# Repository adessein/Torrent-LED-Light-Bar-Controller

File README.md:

# Purpose
The purpose of this project is to create a Wifi controller for an orange Axixtech Torrent Led Light Bar.
This device is a safety light device that can be mounted on a vehicule for signaling danger, roadworks...
It is originaly delivered with a very simple control panel made of push buttons.

The purpose of this project is to create a system for the user to be able to control the light bar wirelessly, using his smartphone.

# Realisation

According to [the manual](../master/doc/TORRENT%20Lightbar%20Operation%20Manual.pdf) the bar is controlled by 15 wires. The voltage at these wires should either be 0 or 12V, respectively low and high level. Some wires should be hold at high level continuously of activating functions, more advanced ones requires mode selection by tapping several times on the wire (sending 12V pulses).

I have decided to make the electonic design as simple as possible: 
 - an ESP8266 is the main controllers: it creates a Wifi access point and sends a webpage to the client.
 - when the user select a function, the controller prepare the wire configuration state and pushes these states to shift registers.
 - since the voltae should be 12V, two Darlington NPN transistor arrays are used. Because they are NPN, they will be used to pull down the voltage when their emitter-base votage is positive. Which means that the controller should control using inversed logic (the shift registed should output 0V for the corresponding wire to be set to 12V and 3.3V for the wire to be set to 0V)

.

The ESP8266 micro-controller creates a Wifi access point.  
When connected to it, the user is redirected to a web page where he can change the illumination mode.  

## Code

The ESP8266 code contains the HTML page, therefore all the code is in one file [TorrentBar.ino](../master/TorrentBar/TorrentBar.ino).  
The webpage is also available in the file [TorrentBar.html](../master/doc/TorrentBar.html) for testing purposes.  

## Electronics

The circuit is rather simple, based on Darlington NPN transistor arrays and shift registers.  
The car battery supplies the 12V, which is reduced to 5V using a LM7805 voltage regulator.  
The 3.3V is either supplied by a LD1117V33 regulator (optional) or by the regulator located on the ESP8266 D1 Mini board.  

[My EDA project can be found here](https://easyeda.com/arnaud.dessein/torrent-light-bar)

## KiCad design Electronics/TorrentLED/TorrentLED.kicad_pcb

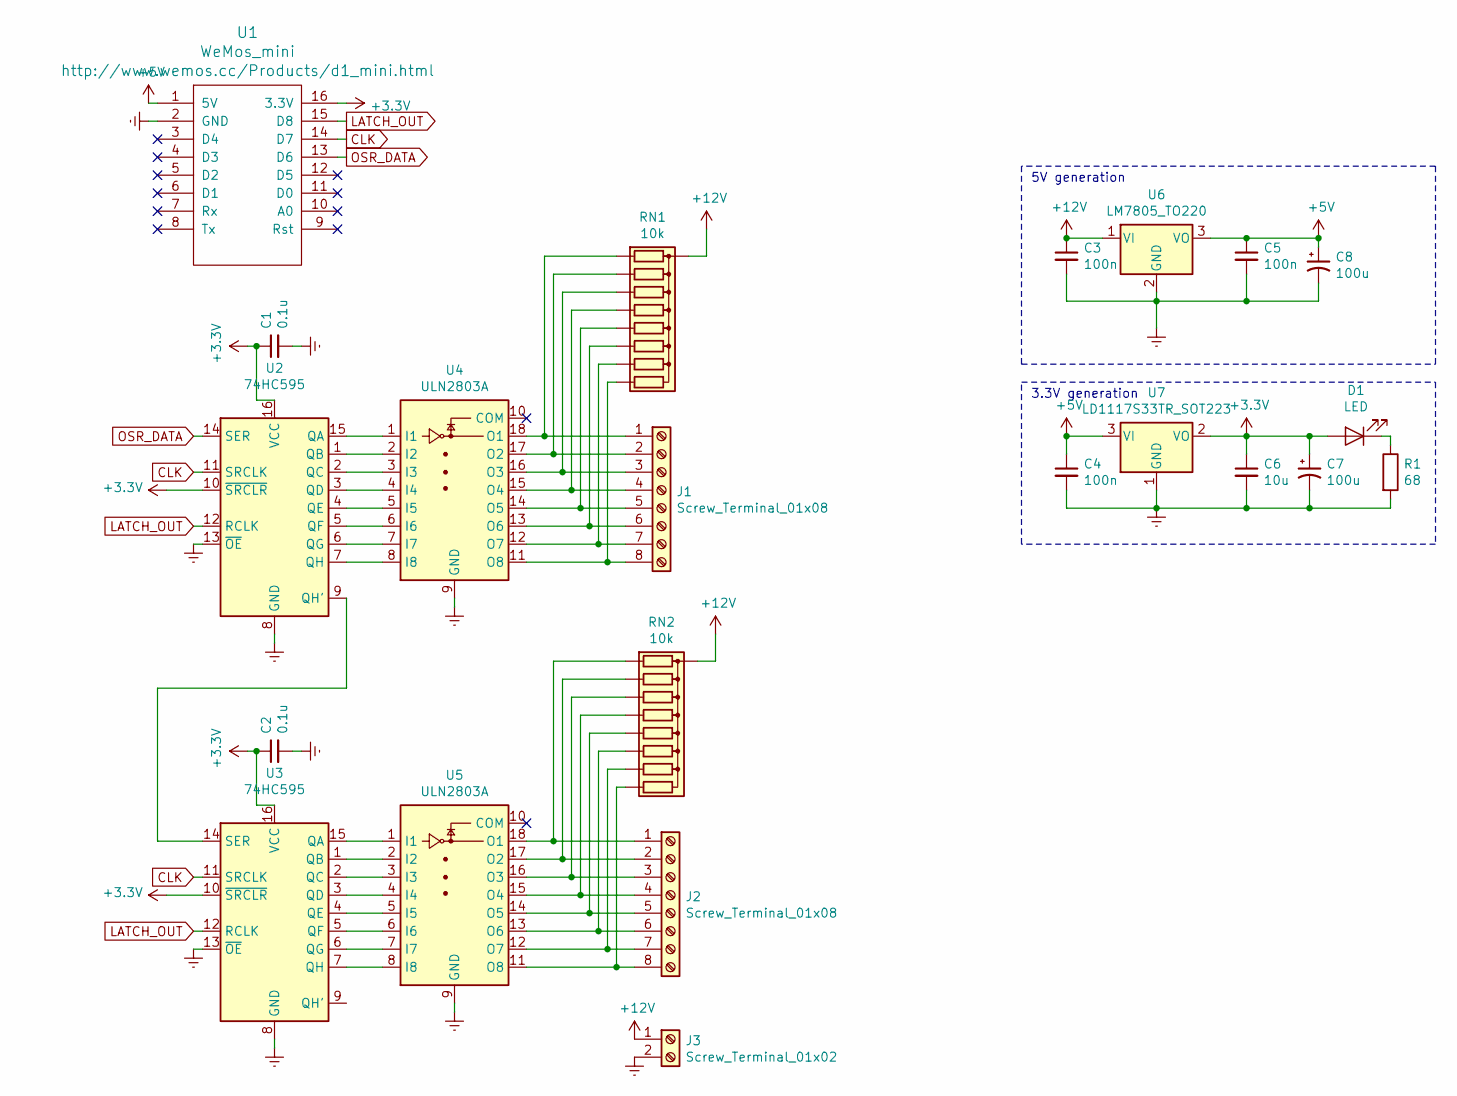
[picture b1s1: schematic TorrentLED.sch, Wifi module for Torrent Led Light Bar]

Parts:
C1, C2: 0.1u; C_Disc_D5.0mm_W2.5mm_P2.50mm
C3, C4, C5: 100n; C_Disc_D5.0mm_W2.5mm_P2.50mm
C6: 10u; C_Radial_D5.0mm_H11.0mm_P2.00mm
C7, C8: 100u; C_Radial_D6.3mm_H11.0mm_P2.50mm
D1: LED; LED_D3.0mm
J1, J2: Screw_Terminal_01x08; TerminalBlock_Phoenix_PT-1,5-8-5.0-H_1x08_P5.00mm_Horizontal
J3: Screw_Terminal_01x02; TerminalBlock_Phoenix_PT-1,5-2-5.0-H_1x02_P5.00mm_Horizontal
R1: 68; R_Axial_DIN0204_L3.6mm_D1.6mm_P7.62mm_Horizontal
RN1, RN2: 10k; R_Array_SIP9
U1: WeMos_mini; D1_mini_board
U2, U3: 74HC595; DIP-16_W7.62mm_Socket
U4, U5: ULN2803A; DIP-18_W7.62mm_Socket
U6: LM7805_TO220; TO-220-3_Vertical
U7: LD1117S33TR_SOT223; TO-220-3_Vertical

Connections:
+3V3: C1.1, C2.1, C6.1, C7.1, D1.2 (A), U1.16 (3.3V), U2.10 (~SRCLR), U2.16 (VCC), U3.10 (~SRCLR), U3.16 (VCC), U7.2 (VO)
+5V: C4.1, C5.1, C8.1, U1.1 (5V), U6.3 (VO), U7.3 (VI)
+12V: C3.1, J3.1, RN1.1 (common), RN2.1 (common), U6.1 (VI)
CLK: U1.14 (D7), U2.11 (SRCLK), U3.11 (SRCLK)
Earth: C1.2, C2.2, C3.2, C4.2, C5.2, C6.2, C7.2, C8.2, J3.2, R1.2, U1.2 (GND), U2.8 (GND), U2.13 (~OE), U3.8 (GND), U3.13 (~OE), U4.9 (GND), U5.9 (GND), U6.2 (GND), U7.1 (GND)
LATCH_OUT: U1.15 (D8), U2.12 (RCLK), U3.12 (RCLK)
unnamed: D1.1 (K), R1.1
unnamed: J1.1, RN1.2 (R1), U4.18 (O1)
unnamed: J1.2, RN1.3 (R2), U4.17 (O2)
unnamed: J1.3, RN1.4 (R3), U4.16 (O3)
unnamed: J1.4, RN1.5 (R4), U4.15 (O4)
unnamed: J1.5, RN1.6 (R5), U4.14 (O5)
unnamed: J1.6, RN1.7 (R6), U4.13 (O6)
unnamed: J1.7, RN1.8 (R7), U4.12 (O7)
unnamed: J1.8, RN1.9 (R8), U4.11 (O8)
unnamed: J2.1, RN2.2 (R1), U5.18 (O1)
unnamed: J2.2, RN2.3 (R2), U5.17 (O2)
unnamed: J2.3, RN2.4 (R3), U5.16 (O3)
unnamed: J2.4, RN2.5 (R4), U5.15 (O4)
unnamed: J2.5, RN2.6 (R5), U5.14 (O5)
unnamed: J2.6, RN2.7 (R6), U5.13 (O6)
unnamed: J2.7, RN2.8 (R7), U5.12 (O7)
unnamed: J2.8, RN2.9 (R8), U5.11 (O8)
unnamed: U2.1 (QB), U4.2 (I2)
unnamed: U2.2 (QC), U4.3 (I3)
unnamed: U2.3 (QD), U4.4 (I4)
unnamed: U2.4 (QE), U4.5 (I5)
unnamed: U2.5 (QF), U4.6 (I6)
unnamed: U2.6 (QG), U4.7 (I7)
unnamed: U2.7 (QH), U4.8 (I8)
unnamed: U2.9 (QH'), U3.14 (SER)
unnamed: U2.15 (QA), U4.1 (I1)
unnamed: U3.1 (QB), U5.2 (I2)
unnamed: U3.2 (QC), U5.3 (I3)
unnamed: U3.3 (QD), U5.4 (I4)
unnamed: U3.4 (QE), U5.5 (I5)
unnamed: U3.5 (QF), U5.6 (I6)
unnamed: U3.6 (QG), U5.7 (I7)
unnamed: U3.7 (QH), U5.8 (I8)
unnamed: U3.15 (QA), U5.1 (I1)
OSR_DATA: U1.13 (D6), U2.14 (SER)

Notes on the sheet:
5V generation
3.3V generation

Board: 2 copper layers, 22 parts (0 on the bottom side), 41 nets, no tracks yet.

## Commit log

2019-06-10 README and documentation
2019-06-10 Small mistake in README
2019-06-10 Small mistake in README (yet another attempt)
2019-06-11 Started to work on the ESP8266 program and the web page controlling the led bar
2019-06-12 Changed the HTML code so the checkboxes will triger the form submit when they are clicked, whatever their state. Then I added tags {Cn} that are modified in the ESP8266 program by the actual state of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
2019-06-12 Small changed
2019-06-13 Major update. Added all functions. Added control of the shift registers. Corrected some labels in webpage. Added debug messages on serial. I still have a problem with the page reloading several time 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
2019-06-14 Simplified the code. Added a hidden parameter to make the difference between user and browser requests. Updated README with the final PCB and SCH (I have ordered the PCBs).
2019-06-14 Moved miscellaneous files to folder doc. Improved README
2019-06-16 Important changes - all features, CSS, FS
    The webpage that I have done before was not adapted to the complex way of
    controlling the bar. Indeed, reading the manual thoroughly made me
    understand that some modes could be programmed and that some features
    (modifiers) where incompatible with certain modes.
    I have separated the webpage from the ino file (it was embended as a
    const char[] defore). Now the webpage is only in the .html file, also
2019-06-26 (WIP) Use jQuery, POST requests and ajax
    Still under development and to be tested.
    I am following the idea that any change of any control should
    trigger a POST request. In order to avoid the refreshing and
    clearing of the form, I return false.
    Indeed, I have abandoned the idea that the server should send a
    new page at every request, reflecting the changes. I prefer to
2019-07-31 Added sendCSS() and dumpArgs()
    Now the programs dumps the arguments received via POST on serial
2019-07-31 First version of the enclosure
    Added Box.cb in Mechanics
2019-10-27 Working on making PCB with KiCad
2021-10-14 Fixing order of bytes and progtam
2021-10-21 Make server a REST interface returning state JSON
2021-10-22 Switches toggle on server's response
2021-10-22 Improving state update
2021-10-25 Server receives JSON. Wait icon
2021-10-26 Saves configuration as JSON file in SSPIFS
2021-10-26 Bug fixes
2021-11-03 Cosmetic changes
2021-11-03 Bug fixes and debug with the bar
2021-11-03 Improves documentation
